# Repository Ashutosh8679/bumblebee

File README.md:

# bumblebee
Bumblebee is a gesture-controlled surveillance robot that uses computer vision for input and a self-hosted WiFi access point for communication. The system combines custom hardware, firmware, and software into a unified robotics platform.

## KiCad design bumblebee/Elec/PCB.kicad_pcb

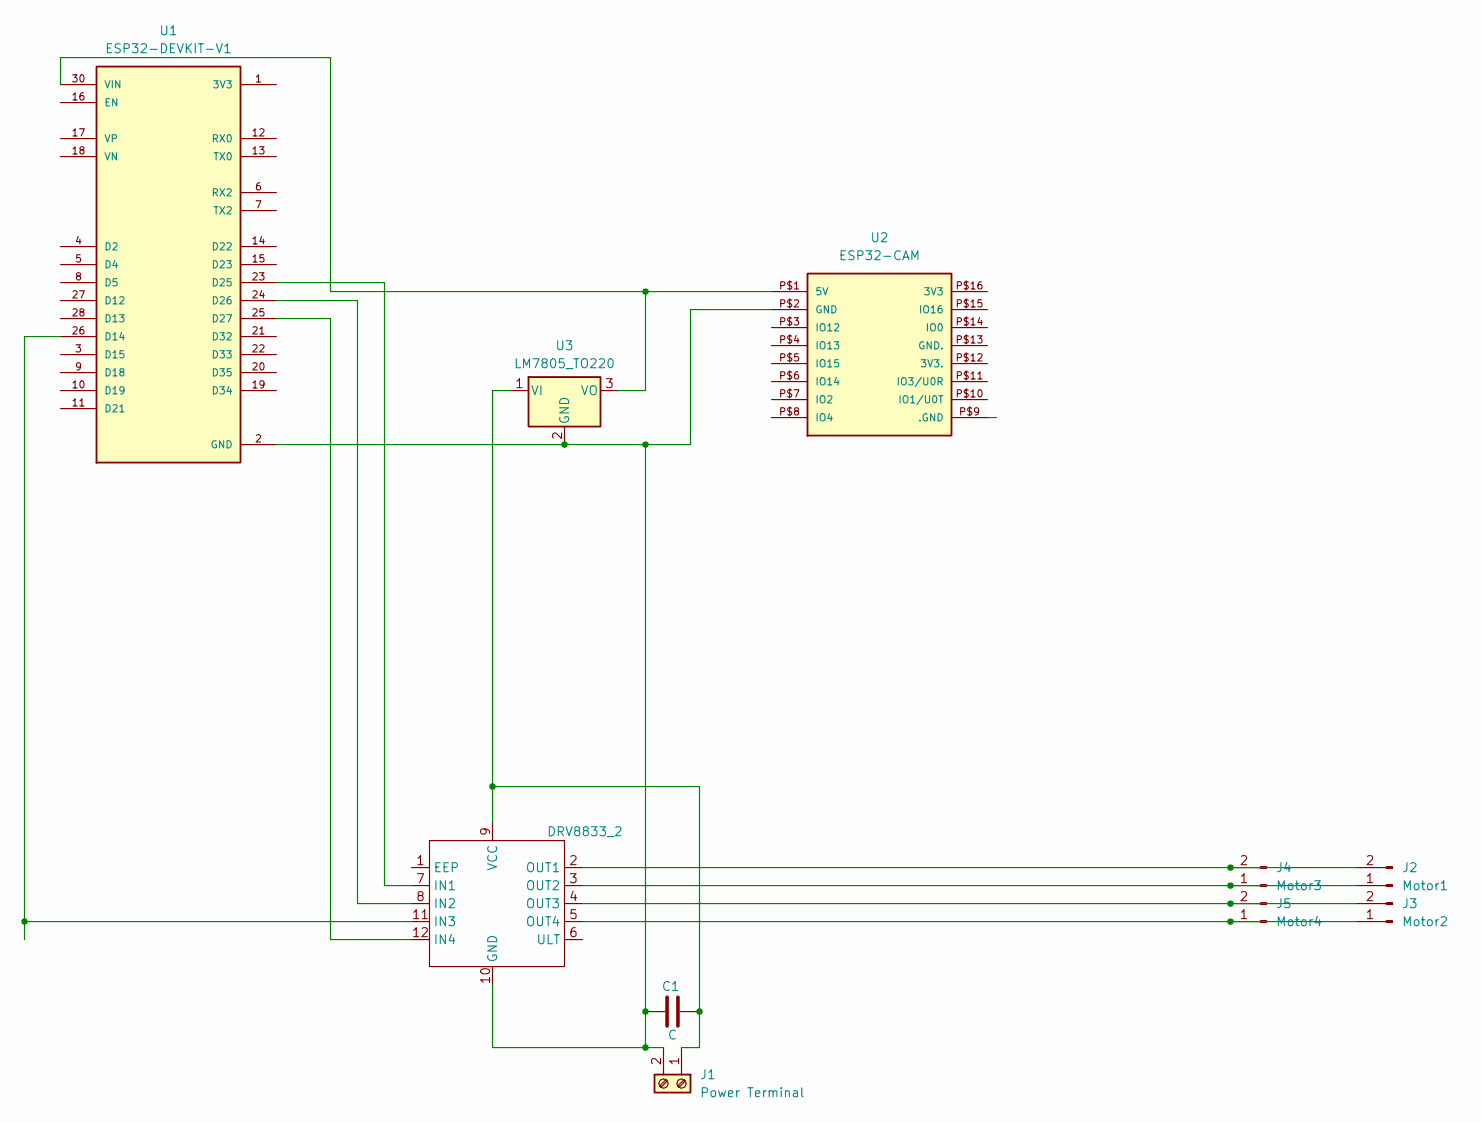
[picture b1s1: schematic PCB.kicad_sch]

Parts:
C1: C; CP_Radial_D10.0mm_P5.00mm
DRV8833_2: DRV8833
J1: Power Terminal; TerminalBlock_MetzConnect_Type011_RT05502HBLC_1x02_P5.00mm_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
J2: Motor1; PinHeader_1x02_P2.54mm_Vertical
J3: Motor2; PinHeader_1x02_P2.54mm_Vertical
J4: Motor3; PinHeader_1x02_P2.54mm_Vertical
J5: Motor4; PinHeader_1x02_P2.54mm_Vertical
U1: ESP32-DEVKIT-V1; MODULE_ESP32_DEVKIT_V1; PARTREV N/A
U2: ESP32-CAM
U3: LM7805_TO220; TO-220-3_Vertical

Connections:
GND: C1.1, DRV8833_2.10 (GND), J1.2, U1.2 (GND), U1.29 (GND), U2.P$2 (GND), U3.2 (GND)
unnamed: DRV8833_2.7 (IN1), U1.23 (D25)
unnamed: DRV8833_2.8 (IN2), U1.24 (D26)
unnamed: DRV8833_2.11 (IN3), U1.26 (D14)
unnamed: DRV8833_2.12 (IN4), U1.25 (D27)
unnamed: DRV8833_2.2 (OUT1), J2.2, J4.2
unnamed: DRV8833_2.3 (OUT2), J2.1, J4.1
unnamed: DRV8833_2.4 (OUT3), J3.2, J5.2
unnamed: DRV8833_2.5 (OUT4), J3.1, J5.1
unnamed: C1.2, DRV8833_2.9 (VCC), J1.1, U3.1 (VI)
unnamed: U1.30 (VIN), U2.P$1 (5V), U3.3 (VO)

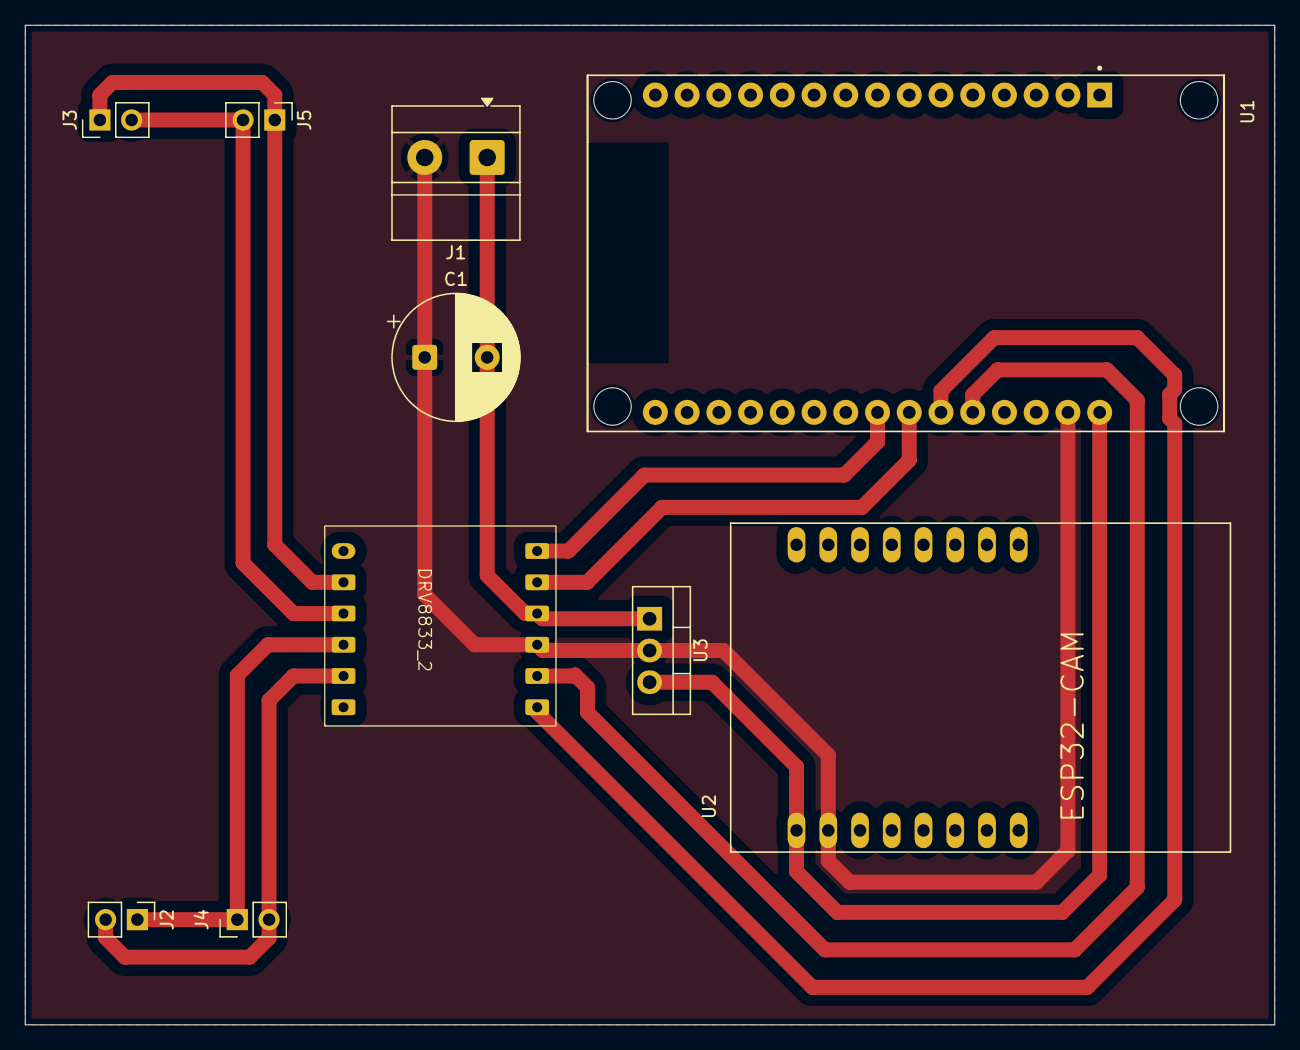
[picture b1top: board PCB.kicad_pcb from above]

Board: 2 copper layers, 100.0 x 80.0 mm, 10 parts (0 on the bottom side), 11 nets.
